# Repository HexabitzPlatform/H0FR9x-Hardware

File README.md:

# H0FR9x-Hardware
Hexabitz 230V/10A(RMS) Enhanced SPDT Relay Module Hardware Design

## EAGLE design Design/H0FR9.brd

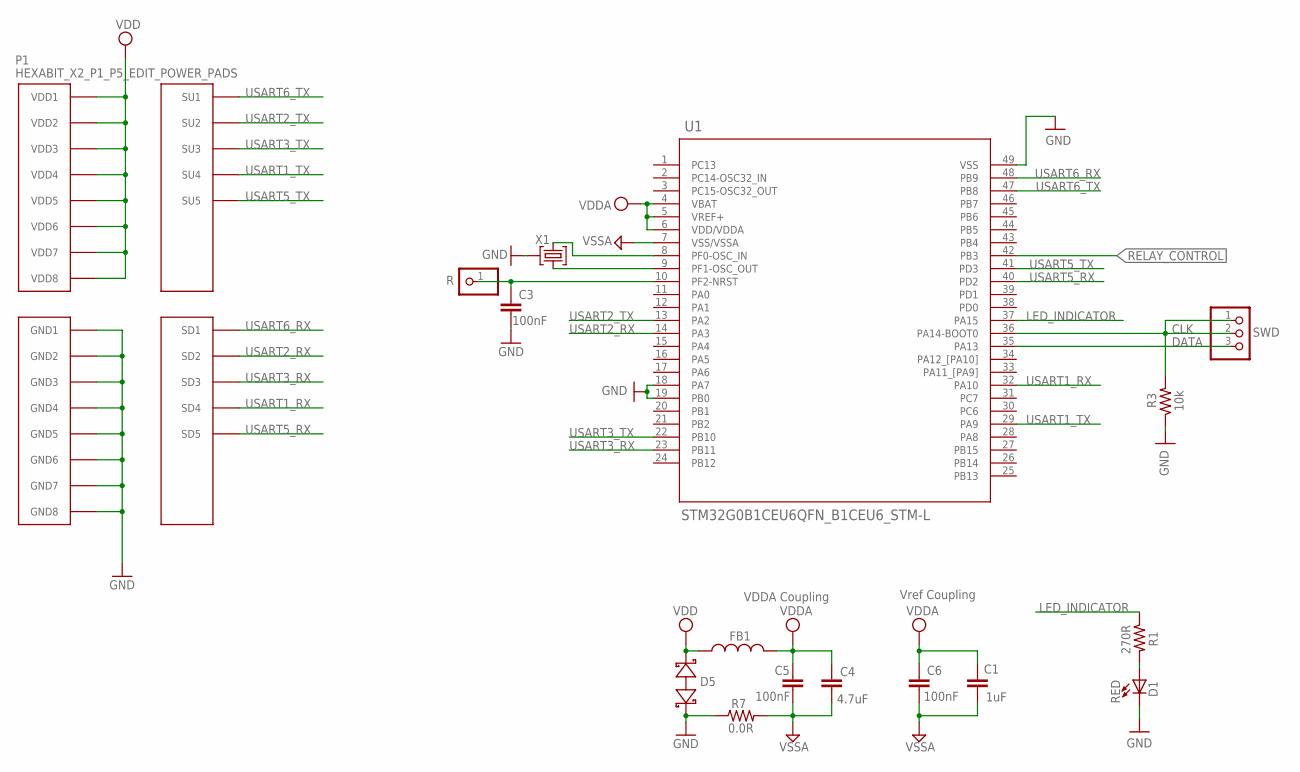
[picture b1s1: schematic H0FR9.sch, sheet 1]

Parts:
C1: 1uF; C-0805; TOLERANCE 10%; VOLTAGE_RATING 16V; MPN CC0805KKX7R7BB105
C3, C5: 100nF; C-0603
C4: 4.7uF; C-0805; TOLERANCE 10%; VOLTAGE_RATING 25V; MPN GRM21BC81E475KA12L
C6: 100nF; C-0603; TOLERANCE 10%; VOLTAGE_RATING 10V; MPN C0603C104K8RACTU
D1: RED; VLMS1300-GS08; MPN VLMS1300-GS08
D5: BOURNS_CDSOD323-T03SCBOURNS_CDSOD323-T03SC_0_0; BOURNS_CDSOD323-T03SC_0
FB1: FB-0603
P1: HEXABIT_X2_P1_P5_EDIT_POWER_PADS
R: R; 1X01
R1: 270R; R-0603
R3: 10k; R-0603; TOLERANCE 5%; MPN RC0603JR-0710KL
R7: 0.0R; R-0603
SWD: PINHD-1X3SWD; SWD
TRIMBLE-LOGO2: HEXA-LOGO
U1: STM32G0B1CEU6QFN_B1CEU6_STM-L; QFN_B1CEU6_STM-L
X1: XTALL_CSTCE8M00G52

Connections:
CLK: R3.2, SWD.1, SWD.2, U1.36 (PA14-BOOT0)
DATA: SWD.3, U1.35 (PA13)
GND: C3.2, D1.C, D5.2 (C), P1.PAD_PD11 (GND1), P1.PAD_PD12 (GND2), P1.PAD_PD13 (GND3), P1.PAD_PD14 (GND4), P1.PAD_PD17 (GND5), P1.PAD_PD18 (GND6), P1.PAD_PD19 (GND7), P1.PAD_PD20 (GND8), R3.1, R7.1, U1.18 (PA7), U1.19 (PB0), U1.49 (VSS), X1.P$2 (2); also elsewhere on the board
LED_INDICATOR: R1.1, U1.37 (PA15)
unnamed: D1.A, R1.2
unnamed: C3.1, R.1, U1.10 (PF2-NRST)
unnamed: U1.9 (PF1-OSC_OUT), X1.P$1 (1)
unnamed: U1.8 (PF0-OSC_IN), X1.P$3 (3)
RELAY_CONTROL: U1.42 (PB3); also elsewhere on the board
USART1_RX: P1.PAD_PD4 (SD4), U1.32 (PA10)
USART1_TX: P1.PAD_PU4 (SU4), U1.29 (PA9)
USART2_RX: P1.PAD_PD2 (SD2), U1.14 (PA3)
USART2_TX: P1.PAD_PU2 (SU2), U1.13 (PA2)
USART3_RX: P1.PAD_PD3 (SD3), U1.23 (PB11)
USART3_TX: P1.PAD_PU3 (SU3), U1.22 (PB10)
USART5_RX: P1.PAD_PD5 (SD5), U1.40 (PD2)
USART5_TX: P1.PAD_PU5 (SU5), U1.41 (PD3)
USART6_RX: P1.PAD_PD1 (SD1), U1.48 (PB9)
USART6_TX: P1.PAD_PU1 (SU1), U1.47 (PB8)
VDD: D5.1 (A), FB1.1, P1.PAD_PU11 (VDD1), P1.PAD_PU12 (VDD2), P1.PAD_PU13 (VDD3), P1.PAD_PU14 (VDD4), P1.PAD_PU17 (VDD5), P1.PAD_PU18 (VDD6), P1.PAD_PU19 (VDD7), P1.PAD_PU20 (VDD8); also elsewhere on the board
VDDA: C1.1, C4.1, C5.1, C6.1, FB1.2, U1.4 (VBAT), U1.5 (VREF+), U1.6 (VDD/VDDA)
VSSA: C1.2, C4.2, C5.2, C6.2, R7.2, U1.7 (VSS/VSSA)

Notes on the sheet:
Vref Coupling
VDDA Coupling

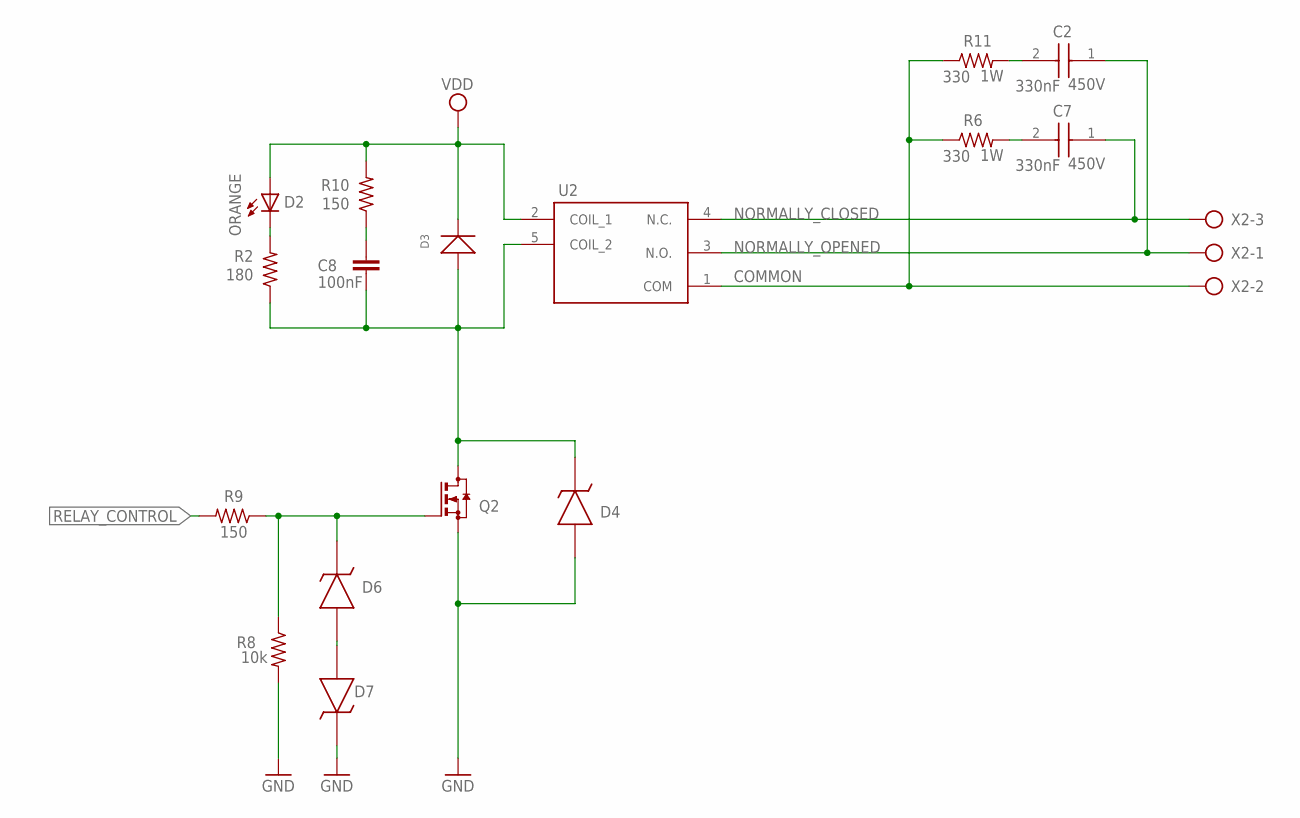
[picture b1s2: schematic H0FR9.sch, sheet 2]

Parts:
C2, C7: 330nF; B32922Q_(18_X_8.5)
C8: 100nF; C-0603; TOLERANCE 10%; VOLTAGE_RATING 10V; MPN C0603C104K8RACTU
D2: ORANGE; VLMS1300-GS08; MPN VLMY1300-GS08
D3: 40V 300MA; SOD-323
D4: MMSZ4705T1GMMSZ4705T1G; DIO_MMSZ4700T1G; MPN MMSZ4705T1G
D6, D7: MMSZ4705T1GMMSZ4705T1G; DIO_MMSZ4700T1G; MPN MMSZ5231BT3G
Q2: BSS123; SOT23
R2: 180; R-0603; TOLERANCE ±5%; MPN ERJ-3GEYJ181V
R6, R11: 330; R2512; MPN RMCF2512JT330R
R8: 10k; R-0603; TOLERANCE 5%; MPN RC0603JR-07680KL
R9, R10: 150; R-0603; TOLERANCE 5%; MPN RC0603JR-07680KL
U2: G5LE-14_DC3; G5LE-14_SPDT
X2: AK300/3; MPN 1715734

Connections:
COMMON: R6.1, R11.1, U2.1 (COM), X2.2
GND: D4.A, D7.K, Q2.2 (S), R8.2; also elsewhere on the board
unnamed: D6.A, D7.A
unnamed: D6.K, Q2.1 (G), R8.1, R9.1
unnamed: D2.C, R2.2
unnamed: C2.2, R11.2
unnamed: C8.1, R10.1
unnamed: C7.2, R6.2
unnamed: C8.2, D3.+, D4.K, Q2.3 (D), R2.1, U2.5 (COIL_2)
NORMALLY_CLOSED: C7.1, U2.4 (N.C.), X2.3
NORMALLY_OPENED: C2.1, U2.3 (N.O.), X2.1
RELAY_CONTROL: R9.2; also elsewhere on the board
VDD: D2.A, D3.-, R10.2, U2.2 (COIL_1); also elsewhere on the board

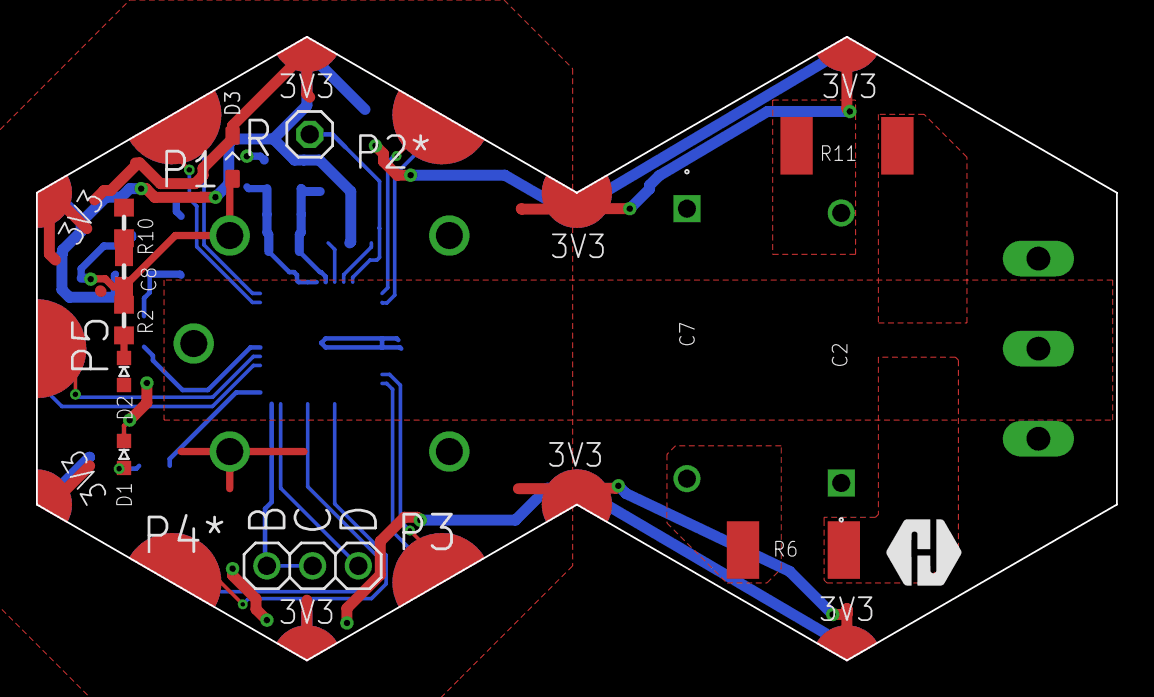
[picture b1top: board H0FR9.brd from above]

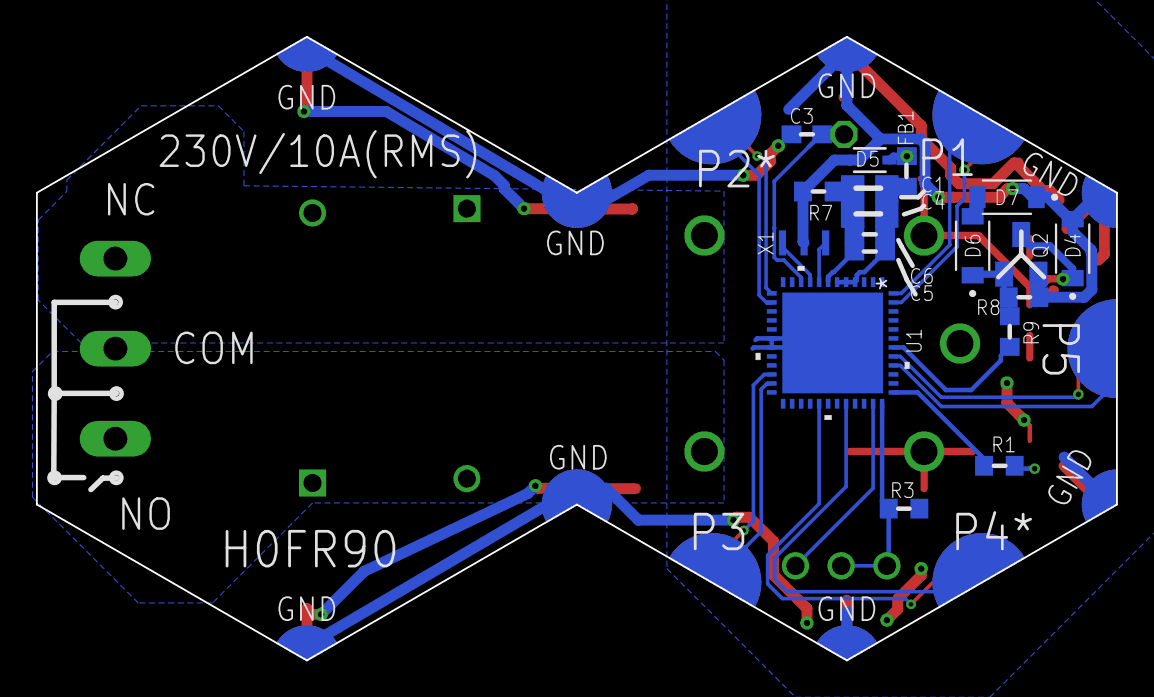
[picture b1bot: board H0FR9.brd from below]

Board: 2 copper layers, 60.0 x 34.6 mm, 34 parts (18 on the bottom side), 32 nets.

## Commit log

2024-07-18 All finish, reviewed version
2024-07-19 Fix BOM

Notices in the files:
parts and their libraries:
COPYRIGHT: Copyright (C) 2021 Ultra Librarian. All rights reserved.
